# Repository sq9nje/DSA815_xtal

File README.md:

# XTAL parameter measurement with Rigol DSA815-TG
This is a tool that automates the process of measuring quarz crystal oscillator parameters using a Rigol DSA815-TG spectrum analyzer with the tracking generator option. You will also need a measuring fixture as described by Jack K8ZOA in "Crystal Motional Parameters: A Comparison of Measurement Approaches"

This tool uses what is known as the "-3dB method" to measure the crystal motional parameters. It lets you easily measure parameters of large batches of XTALs and produces a nice Excel spreadsheet.

### Prerequisites
- Rigol DSA815-TG spectrum analyzer with tracking gen
- Advanced Measurement Kit active license (required for NdB markers)
- Rigol SigmaView for SCPI controll

### Measurement fixture
A simple measurement fixture is required to measure the XTAL parameters using this method. This fixture consists of two PI attenuators that aim to match 50 ohm input and output of the spectrum analyzer to 12.5 ohms and a socket for the DUT. A short link is inserted in place of the crystal for calibration.

Full KiCAD project documentation for this fixture is included in this repository. The board uses SMA connectors and 0805 1% resistors. A short piece of a precision IC socket can be used for the XTAL.

### Measurement procedure
1. Connect spectrum analyzer to computer using USB
2. Connect XTAL fixture to the spectrum analyzer
3. Enable tracking generator
4. Insert a link in place of an XTAL and perform TG normalisation
5. Insert sample XTAL into fixture and set frequency span and amplitude so that the resonance is clearly visible
6. Run script

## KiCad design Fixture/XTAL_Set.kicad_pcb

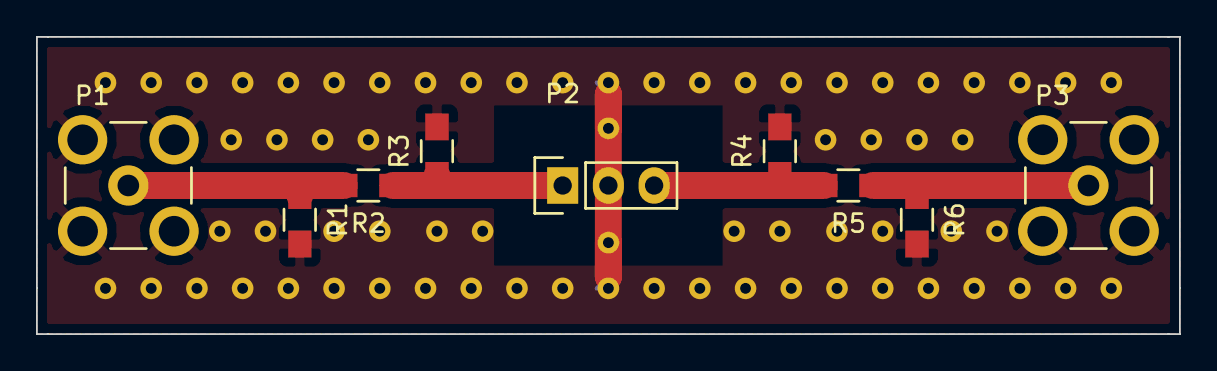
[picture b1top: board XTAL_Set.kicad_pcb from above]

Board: 2 copper layers, 63.5 x 16.5 mm, 9 parts (0 on the bottom side), 5 nets.

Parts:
P1, P3: BNC; SMB_Straight
P2: CONN_01X03; Socket_Strip_Straight_1x03
R1, R6: 158R; R_0805_HandSoldering
R2, R5: 66R5; R_0805_HandSoldering
R3, R4: 14R3; R_0805_HandSoldering

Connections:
GND: P1.2, P2.2, P3.2, R1.2, R3.2, R4.2, R6.2
unnamed: P1.1, R1.1, R2.2
unnamed: P2.1, R2.1, R3.1
unnamed: P2.3, R4.1, R5.2
unnamed: P3.1, R5.1, R6.1

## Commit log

2017-08-27 Docstrings & some cleanup
2017-08-27 Command line arguments
2017-08-27 Initial README
2017-08-27 Measurement procedure outline
2017-08-27 Number column added
2017-08-28 KiCAD files for Measurement fixture
2017-08-28 Fixture paragraph
2017-08-28 Fixture schematic
2017-08-28 Corrected schematic link
2017-08-28 SVG test
2017-08-28 Use rawgit.com for SVG
2017-09-06 Parameter calculation
2017-09-07 minor error correction
